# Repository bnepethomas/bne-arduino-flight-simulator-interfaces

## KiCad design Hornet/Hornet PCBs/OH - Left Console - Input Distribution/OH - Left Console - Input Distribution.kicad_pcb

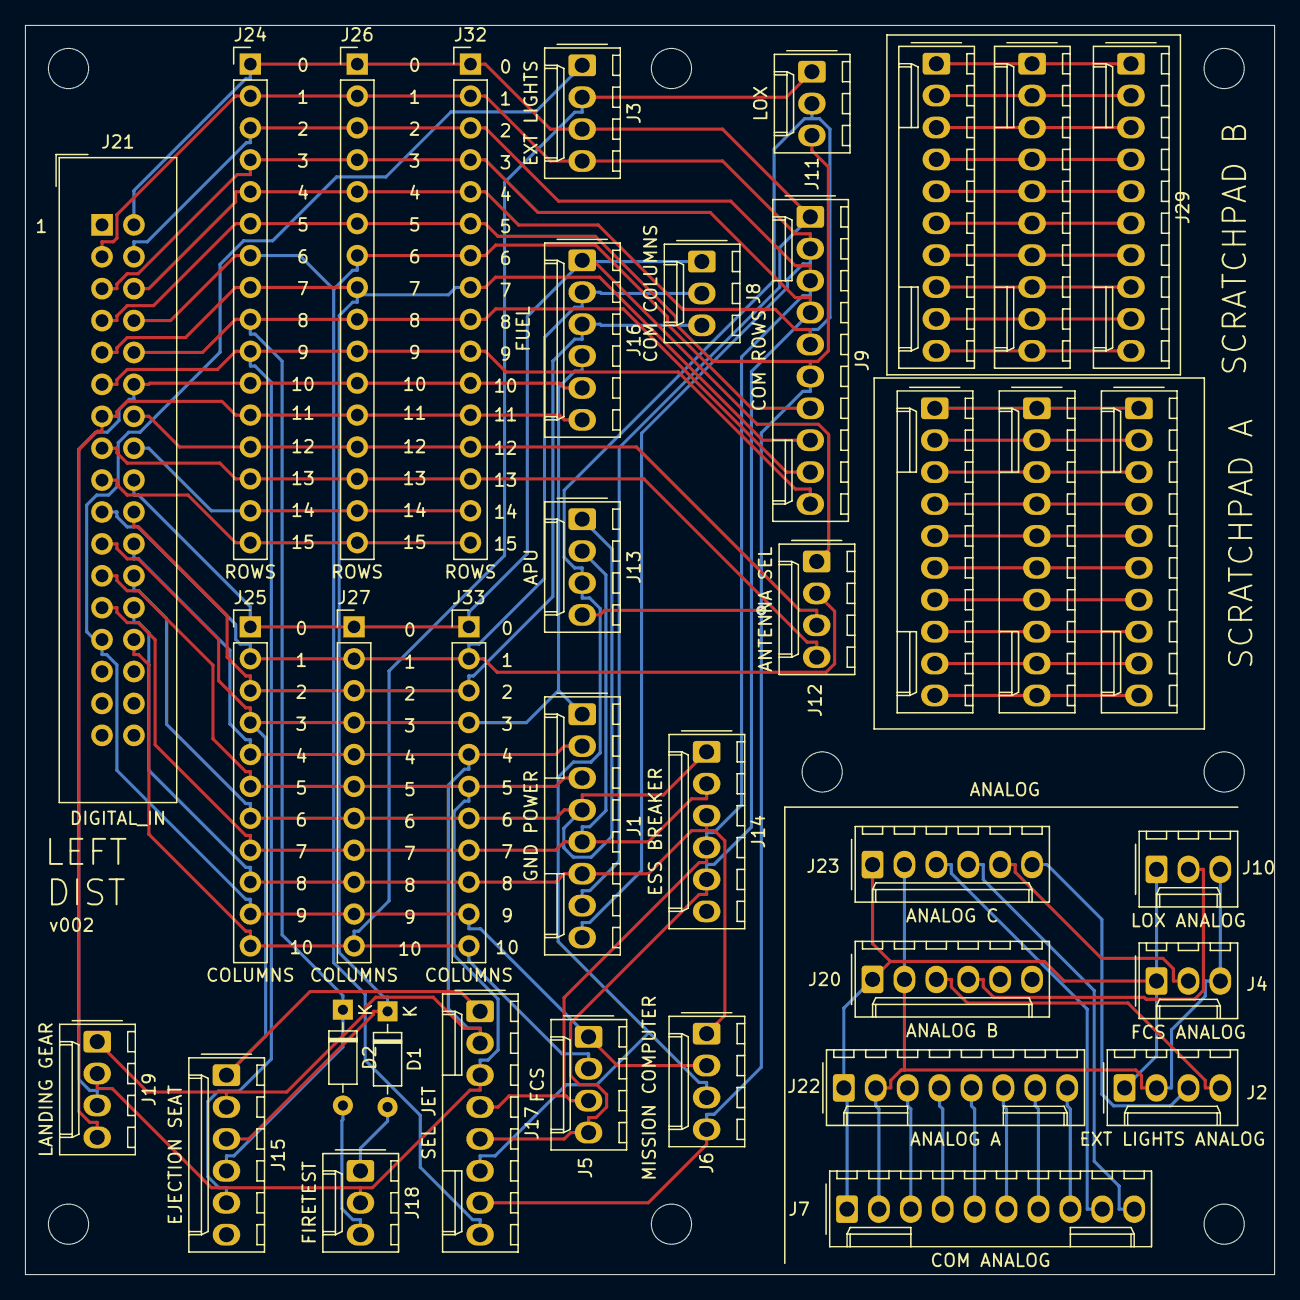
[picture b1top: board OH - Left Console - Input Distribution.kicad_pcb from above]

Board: 2 copper layers, 99.4 x 99.4 mm, 45 parts (0 on the bottom side), 63 nets.

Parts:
D1, D2: D; D_Signal_P7.62mm_Horizontal
H1, H2, H3, H4, H5, H6, H7, H8: MountingHole; MountingHole_3.2mm_M3
J1: GND POWER; Molex_1x08_P2.54mm_Vertical
J2: EXT LIGHTS ANALOG; Molex_1x04_P2.54mm_Vertical
J3: EXT LIGHTS; Molex_1x04_P2.54mm_Vertical
J4: FCS ANALOG; Molex_1x03_P2.54mm_Vertical
J5: FCS; Molex_1x04_P2.54mm_Vertical
J6: MISSION COMPUTER; Molex_1x04_P2.54mm_Vertical
J7: COM ANALOG; Molex_1x10_P2.54mm_Vertical
J8: COM COLUMNS; Molex_1x03_P2.54mm_Vertical
J9: COM ROWS; Molex_1x10_P2.54mm_Vertical
J10: LOX ANALOG; Molex_1x03_P2.54mm_Vertical
J11: LOX; Molex_1x03_P2.54mm_Vertical
J12: ANTENNA SEL; Molex_1x04_P2.54mm_Vertical
J13: APU; Molex_1x04_P2.54mm_Vertical
J14: ESS BREAKER; Molex_1x06_P2.54mm_Vertical
J15: EJECTION SEAT; Molex_1x06_P2.54mm_Vertical
J16: FUEL; Molex_1x06_P2.54mm_Vertical
J17: SEL JET; Molex_1x08_P2.54mm_Vertical
J18: FIRETEST; Molex_1x03_P2.54mm_Vertical
J19: LANDING GEAR; Molex_1x04_P2.54mm_Vertical
J20: ANALOG B; Molex_1x06_P2.54mm_Vertical
J21: DIGITAL_IN; IDC-Header_2x17_P2.54mm_Vertical
J22: ANALOG A; Molex_1x08_P2.54mm_Vertical
J23: ANALOG C; Molex_1x06_P2.54mm_Vertical
J24, J26, J32: ROWS; PinHeader_1x16_P2.54mm_Vertical
J25, J27, J33: COLUMNS; PinHeader_1x11_P2.54mm_Vertical
J28: SpareA1; Molex_1x10_P2.54mm_Vertical
J29: SpareB1; Molex_1x10_P2.54mm_Vertical
J30: SpareA2; Molex_1x10_P2.54mm_Vertical
J31: SpareB2; Molex_1x10_P2.54mm_Vertical
J34: SpareA3; Molex_1x10_P2.54mm_Vertical
J35: SpareB3; Molex_1x10_P2.54mm_Vertical

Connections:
/A1: J28.1, J30.1, J34.1
/A2: J28.2, J30.2, J34.2
/A3: J28.3, J30.3, J34.3
/A4: J28.4, J30.4, J34.4
/A5: J28.5, J30.5, J34.5
/A6: J28.6, J30.6, J34.6
/A7: J28.7, J30.7, J34.7
/A8: J28.8, J30.8, J34.8
/A9: J28.9, J30.9, J34.9
/A10: J28.10, J30.10, J34.10
/ANALOG_5V: J2.1, J4.1, J7.1, J10.1, J20.1, J22.1, J23.1
/ANALOG_GND: J2.2, J4.3, J7.2, J10.3, J20.2, J22.2, J23.2
/B1: J29.1, J31.1, J35.1
/B2: J29.2, J31.2, J35.2
/B3: J29.3, J31.3, J35.3
/B4: J29.4, J31.4, J35.4
/B5: J29.5, J31.5, J35.5
/B6: J29.6, J31.6, J35.6
/B7: J29.7, J31.7, J35.7
/B8: J29.8, J31.8, J35.8
/B9: J29.9, J31.9, J35.9
/B10: J29.10, J31.10, J35.10
/COL0: J8.1, J12.1, J16.1, J21.18, J25.1, J27.1, J33.1
/COL1: J8.2, J12.2, J16.2, J21.19, J25.2, J27.2, J33.2
/COL2: J8.3, J16.3, J21.20, J25.3, J27.3, J33.3
/COL3: J1.1, J15.1, J16.4, J17.1, J21.21, J25.4, J27.4, J33.4
/COL4: J1.2, J15.2, J17.2, J19.1, J21.22, J25.5, J27.5, J33.5
/COL5: J1.3, J17.3, J18.2, J19.2, J21.23, J25.6, J27.6, J33.6
/COL6: J1.4, J13.1, J14.1, J21.24, J25.7, J27.7, J33.7
/COL7: J1.5, J13.2, J14.2, J21.25, J25.8, J27.8, J33.8
/COL8: J1.6, J6.1, J14.3, J21.26, J25.9, J27.9, J33.9
/COL9: J3.1, J5.1, J6.2, J21.27, J25.10, J27.10, J33.10
/COL10: J3.2, J5.2, J11.1, J21.28, J25.11, J27.11, J33.11
/COM_AUX: J7.9, J23.3
/COM_ICS: J7.4, J22.4
/COM_MIDS_A: J7.6, J22.6
/COM_MIDS_B: J7.7, J22.7
/COM_RWR: J7.5, J22.5
/COM_TACAN: J7.8, J22.8
/COM_VOX: J7.3, J22.3
/COM_WPN: J7.10, J23.4
/FORMATION_DIMMER: J2.4, J20.3
/OXY_FLOW: J10.2, J20.4
/POSITION_DIMMER: J2.3, J23.6
/ROW0: J1.7, J3.3, J9.1, J21.2, J24.1, J26.1, J32.1
/ROW1: J1.8, J3.4, J9.2, J21.3, J24.2, J26.2, J32.2
/ROW2: J5.3, J9.3, J14.4, J17.4, J21.4, J24.3, J26.3, J32.3
/ROW3: J5.4, J9.4, J14.5, J17.5, J21.5, J24.4, J26.4, J32.4
/ROW4: J6.3, J9.5, J11.2, J13.3, J17.6, J21.6, J24.5, J26.5, J32.5
/ROW5: J6.4, J9.6, J11.3, J13.4, J17.7, J21.7, J24.6, J26.6, J32.6
/ROW6: J9.7, J17.8, J21.8, J24.7, J26.7, J32.7
/ROW7: D1.1, J9.8, J15.3, J21.9, J24.8, J26.8, J32.8
/ROW8: D2.1, J9.9, J15.4, J21.10, J24.9, J26.9, J32.9
/ROW9: J9.10, J15.5, J21.11, J24.10, J26.10, J32.10
/ROW10: J16.5, J19.3, J21.12, J24.11, J26.11, J32.11
/ROW11: J16.6, J19.4, J21.13, J24.12, J26.12, J32.12
/ROW12: J12.3, J21.14, J24.13, J26.13, J32.13
/ROW13: J12.4, J21.15, J24.14, J26.14, J32.14
/ROW14: J21.16, J24.15, J26.15, J32.15
/ROW15: J21.17, J24.16, J26.16, J32.16
/RUD_TRIM: J4.2, J23.5
unnamed: D1.2, J18.1
unnamed: D2.2, J18.3

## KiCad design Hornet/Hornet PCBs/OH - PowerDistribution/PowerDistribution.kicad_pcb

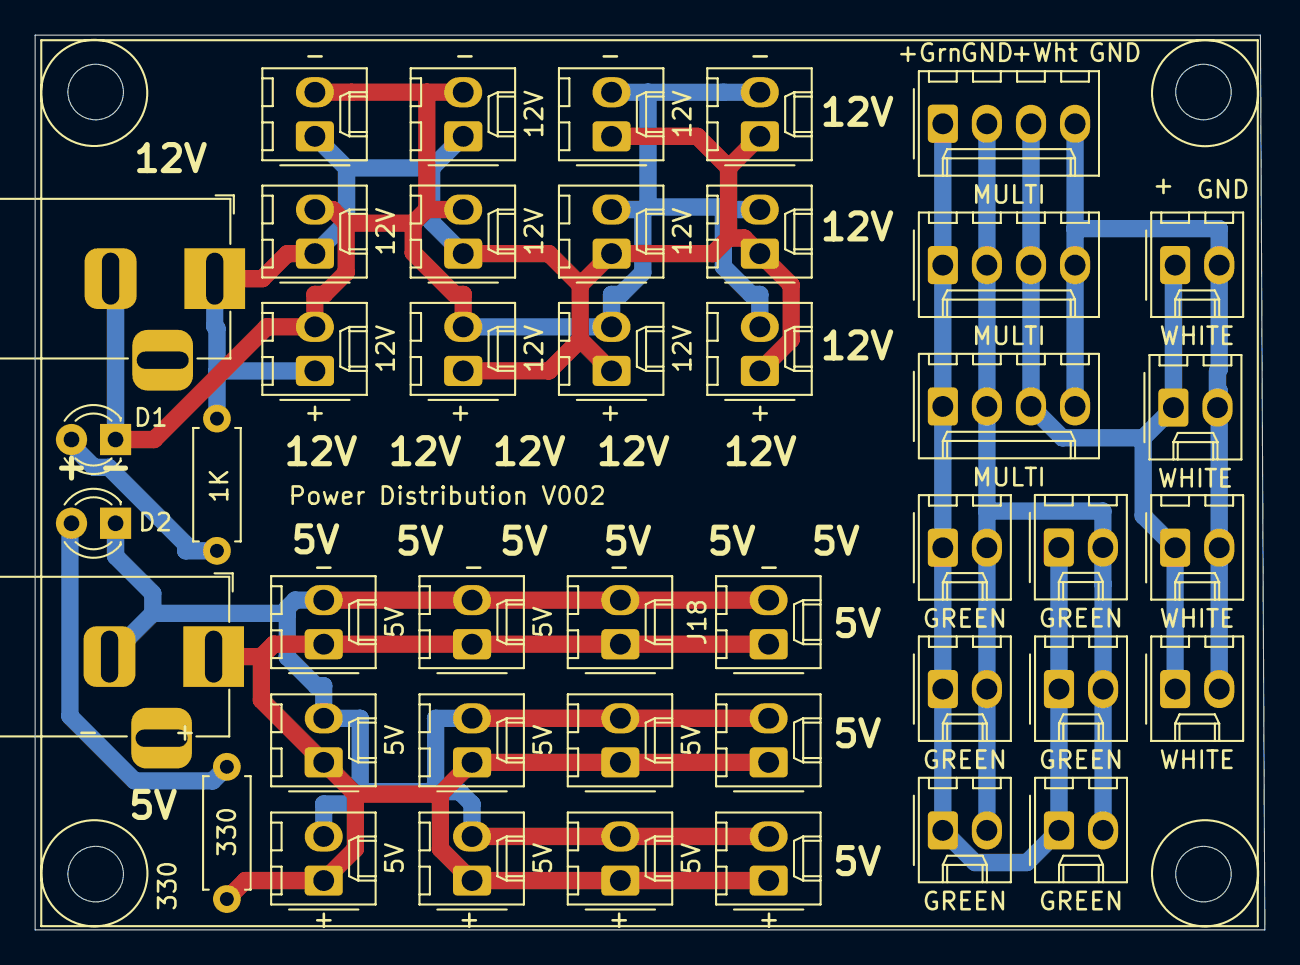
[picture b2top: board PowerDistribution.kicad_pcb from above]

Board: 2 copper layers, 70.9 x 51.6 mm, 48 parts (0 on the bottom side), 10 nets.

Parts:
D1, D2: LED; LED_D3.0mm
H1, H2, H3, H4: MountingHole; MountingHole_3.2mm_M3
J1: 12V; BarrelJack_Horizontal
J2: 5V; BarrelJack_Horizontal
J3, J4, J5: MULTI; Molex_1x04_P2.54mm_Vertical
J6, J7, J11, J12, J16, J17, J23, J24, J28, J29, J34, J35: 12V; Molex_1x02_P2.54mm_Vertical
J8, J9, J14, J15, J21, J22: GREEN; Molex_1x02_P2.54mm_Vertical
J10, J13, J20, J27: WHITE; Molex_1x02_P2.54mm_Vertical
J18, J19, J25, J26, J30, J31, J32, J33, J36, J37, J38, J39: 5V; Molex_1x02_P2.54mm_Vertical
R1: 1K; R_Axial_DIN0207_L6.3mm_D2.5mm_P7.62mm_Horizontal
R2: 330; R_Axial_DIN0207_L6.3mm_D2.5mm_P7.62mm_Horizontal
SPCB1: PT_SmallPCB; PT_General_PCB_Outline

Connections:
/5VGND: D2.1, J2.2, J18.2, J19.2, J25.2, J26.2, J30.2, J31.2, J32.2, J33.2, J36.2, J37.2, J38.2, J39.2
/12VGND: D1.1, J1.2, J6.2, J7.2, J11.2, J12.2, J16.2, J17.2, J23.2, J24.2, J28.2, J29.2, J34.2, J35.2
/+5V: J2.1, J18.1, J19.1, J25.1, J26.1, J30.1, J31.1, J32.1, J33.1, J36.1, J37.1, J38.1, J39.1, R2.1
/+12V: J1.1, J6.1, J7.1, J11.1, J12.1, J16.1, J17.1, J23.1, J24.1, J28.1, J29.1, J34.1, J35.1, R1.1
/Green12V+: J3.1, J4.1, J5.1, J8.1, J9.1, J14.1, J15.1, J21.1, J22.1
/GreenGND: J3.2, J4.2, J5.2, J8.2, J9.2, J14.2, J15.2, J21.2, J22.2
/White+12V: J3.3, J4.3, J5.3, J10.1, J13.1, J20.1, J27.1
/WhiteGND: J3.4, J4.4, J5.4, J10.2, J13.2, J20.2, J27.2
unnamed: D1.2, R1.2
unnamed: D2.2, R2.2

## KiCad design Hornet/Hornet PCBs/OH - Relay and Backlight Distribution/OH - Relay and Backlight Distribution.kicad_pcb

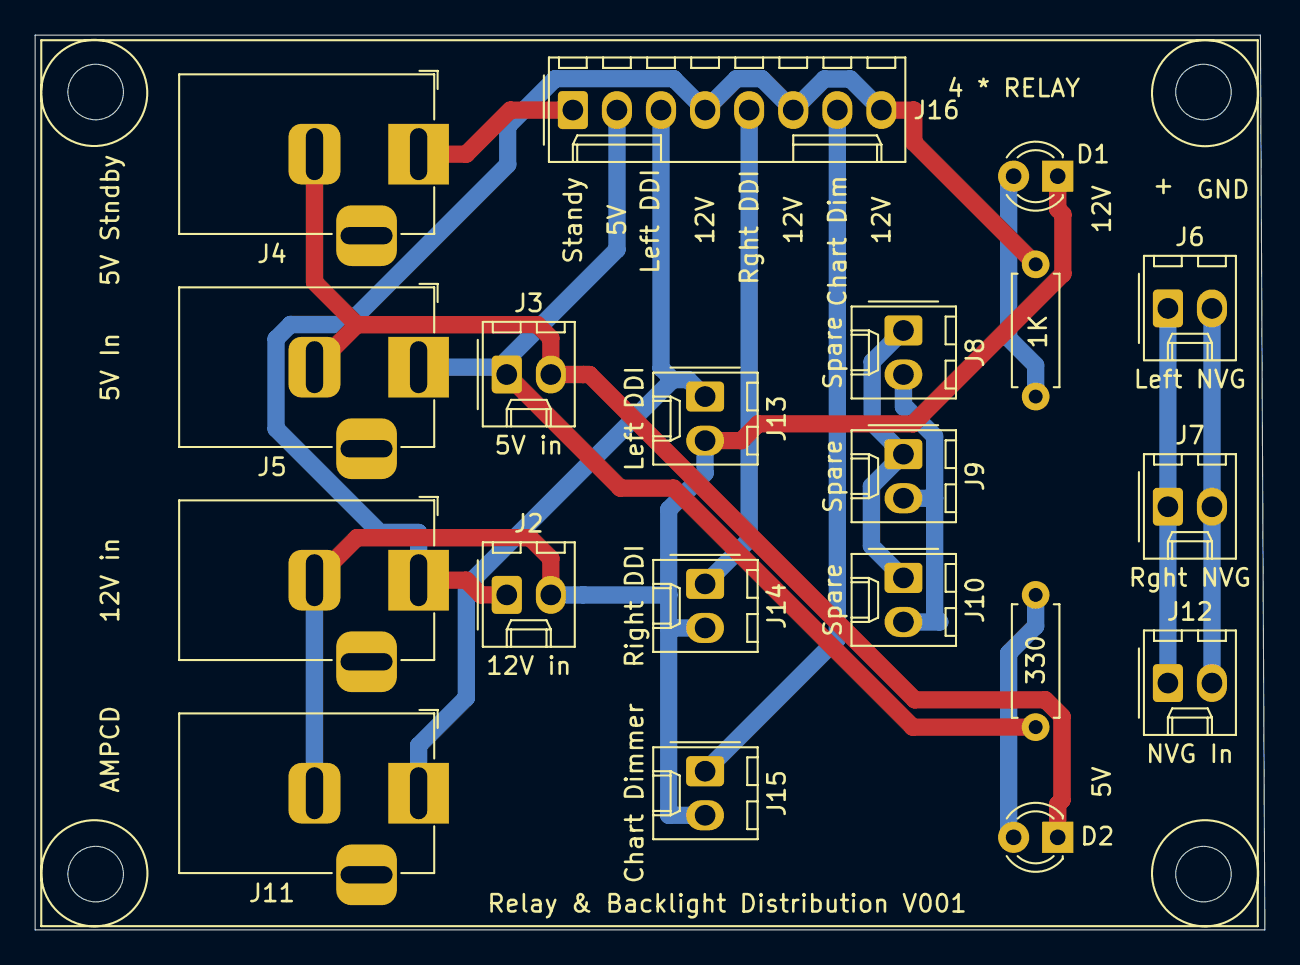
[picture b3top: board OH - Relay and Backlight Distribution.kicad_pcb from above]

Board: 2 copper layers, 70.9 x 51.6 mm, 25 parts (0 on the bottom side), 14 nets.

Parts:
D1, D2: LED; LED_D3.0mm
H1, H2, H3, H4: MountingHole; MountingHole_3.2mm_M3
J1: 12V in; BarrelJack_Horizontal
J2: 12V in; Molex_KK-254_AE-6410-02A_1x02_P2.54mm_Vertical
J3: 5V in; Molex_KK-254_AE-6410-02A_1x02_P2.54mm_Vertical
J4: 5V Stndby; BarrelJack_Horizontal
J5: 5V In; BarrelJack_Horizontal
J6: Left NVG; Molex_KK-254_AE-6410-02A_1x02_P2.54mm_Vertical
J7: Rght NVG; Molex_KK-254_AE-6410-02A_1x02_P2.54mm_Vertical
J8, J9, J10: Spare; Molex_KK-254_AE-6410-02A_1x02_P2.54mm_Vertical
J11: AMPCD; BarrelJack_Horizontal
J12: NVG In; Molex_KK-254_AE-6410-02A_1x02_P2.54mm_Vertical
J13: Left DDI; Molex_KK-254_AE-6410-02A_1x02_P2.54mm_Vertical
J14: Right DDI; Molex_KK-254_AE-6410-02A_1x02_P2.54mm_Vertical
J15: Chart Dimmer; Molex_KK-254_AE-6410-02A_1x02_P2.54mm_Vertical
J16: 4 * RELAY; Molex_KK-254_AE-6410-08A_1x08_P2.54mm_Vertical
R1: 1K; R_Axial_DIN0207_L6.3mm_D2.5mm_P7.62mm_Horizontal
R2: 330; R_Axial_DIN0207_L6.3mm_D2.5mm_P7.62mm_Horizontal
SPCB1: PT_SmallPCB; PT_General_PCB_Outline

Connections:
/5VGND: D2.1, J3.2, J4.2, J5.2
/12VGND: D1.1, J1.2, J2.2, J11.2, J13.2, J14.2, J15.2
/+5VSwitched: J4.1, J16.1
/+5Vin: J3.1, J5.1, J16.2, R2.1
/+12VChartDimmer: J15.1, J16.7
/+12VLeftDDI: J11.1, J13.1, J16.3
/+12VRightDDI: J14.1, J16.5
/+12Vin: J1.1, J2.1, J16.4, J16.6, J16.8, R1.1
/A1: J8.2, J9.2, J10.2
/A2: J8.1, J9.1, J10.1
/NVG+: J6.1, J7.1, J12.1
/NVG-: J6.2, J7.2, J12.2
unnamed: D1.2, R1.2
unnamed: D2.2, R2.2

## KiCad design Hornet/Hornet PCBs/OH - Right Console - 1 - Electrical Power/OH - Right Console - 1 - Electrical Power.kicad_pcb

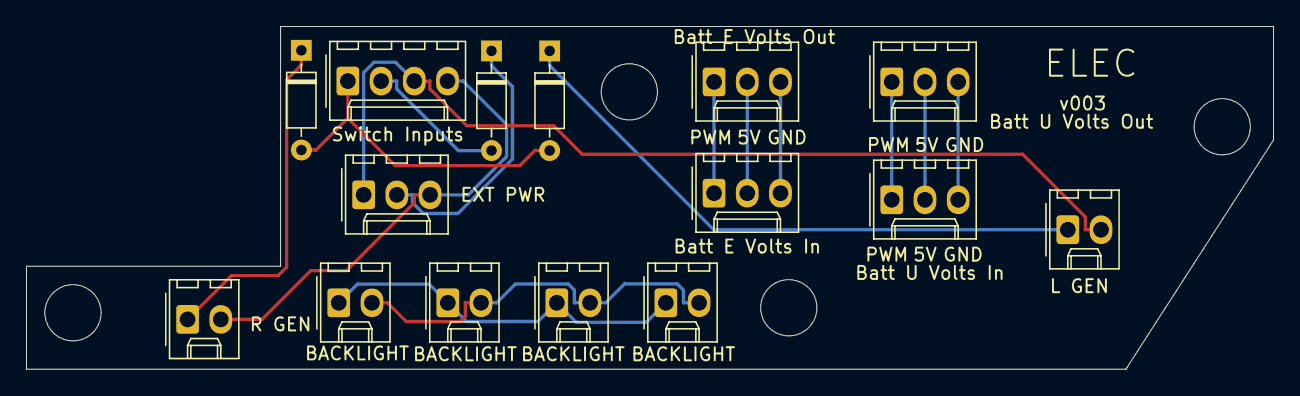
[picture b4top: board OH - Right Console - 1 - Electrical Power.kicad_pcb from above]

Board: 2 copper layers, 95.4 x 26.2 mm, 19 parts (0 on the bottom side), 15 nets.

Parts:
D1, D2, D3: D; D_Signal_P7.62mm_Horizontal
H1, H2, H3, H4: MountingHole; MountingHole_4.3mm_M4
J1: Switch Inputs; Molex_1x04_P2.54mm_Vertical
J2: Batt U Volts In; Molex_1x03_P2.54mm_Vertical
J3: Batt E Volts In; Molex_1x03_P2.54mm_Vertical
J4: Batt U Volts Out; Molex_1x03_P2.54mm_Vertical
J5: Batt E Volts Out; Molex_1x03_P2.54mm_Vertical
J6, J7, J8, J9: BACKLIGHT; Molex_1x02_P2.54mm_Vertical
SW1: EXT PWR; Molex_1x03_P2.54mm_Vertical
SW2: R GEN; Molex_1x02_P2.54mm_Vertical
SW3: L GEN; Molex_1x02_P2.54mm_Vertical

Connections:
/BACKLIGHT+12V: J6.1, J7.1, J8.1, J9.1
/BACKLIGHT-GND: J6.2, J7.2, J8.2, J9.2
/E_5V: J3.2, J5.2
/E_GND: J3.3, J5.3
/E_PWM: J3.1, J5.1
/Row1: J1.3, SW1.1, SW3.2
/Row2: J1.4, SW1.3, SW2.2
/U_5V: J2.2, J4.2
/U_GND: J2.3, J4.3
/U_PWM: J2.1, J4.1
unnamed: D1.1, SW3.1
unnamed: D1.2, D3.2, J1.1
unnamed: D2.1, SW1.2
unnamed: D2.2, J1.2
unnamed: D3.1, SW2.1

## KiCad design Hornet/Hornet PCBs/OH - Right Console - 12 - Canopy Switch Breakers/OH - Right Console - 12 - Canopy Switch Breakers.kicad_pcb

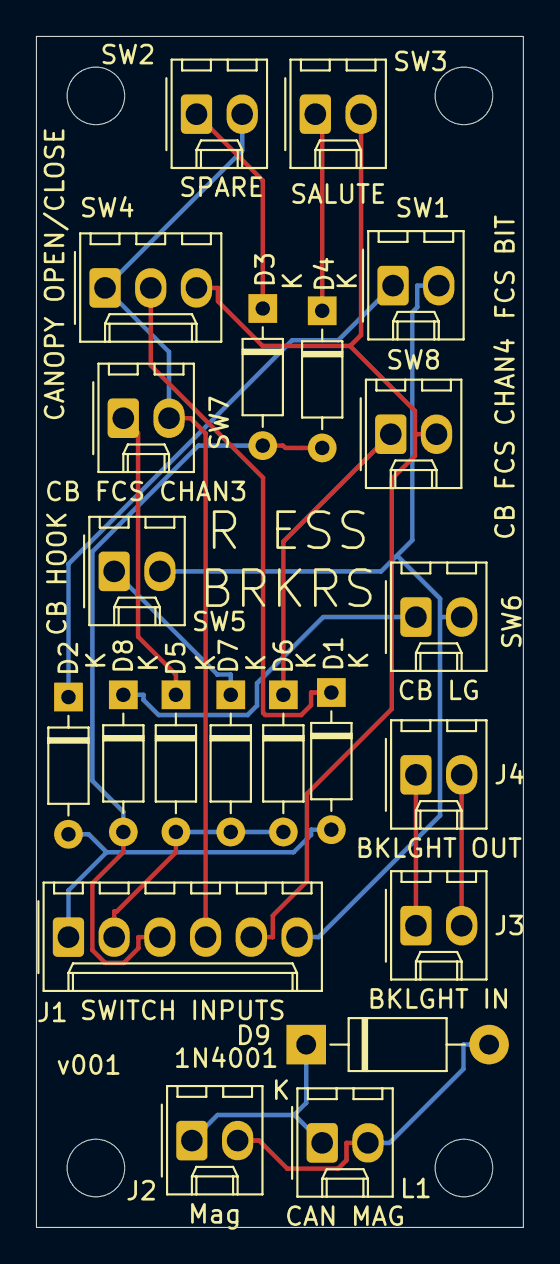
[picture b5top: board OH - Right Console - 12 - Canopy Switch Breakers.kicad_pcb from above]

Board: 2 copper layers, 27.1 x 66.2 mm, 26 parts (0 on the bottom side), 18 nets.

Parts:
D1, D2, D3, D4, D5, D6, D7, D8: D; D_Signal_P7.62mm_Horizontal
D9: 1N4001; D_DO-41_SOD81_P10.16mm_Horizontal
H1, H2, H3, H4: MountingHole; MountingHole_3.2mm_M3
J1: SWITCH INPUTS; Molex_1x06_P2.54mm_Vertical
J2: Mag; Molex_1x02_P2.54mm_Vertical
J3: BKLGHT IN; Molex_1x02_P2.54mm_Vertical
J4: BKLGHT OUT; Molex_1x02_P2.54mm_Vertical
L1: CAN MAG; Molex_1x02_P2.54mm_Vertical
SW1: FCS BIT; Molex_1x02_P2.54mm_Vertical
SW2: SPARE; Molex_1x02_P2.54mm_Vertical
SW3: SALUTE; Molex_1x02_P2.54mm_Vertical
SW4: CANOPY OPEN/CLOSE; Molex_1x03_P2.54mm_Vertical
SW5: CB HOOK; Molex_1x02_P2.54mm_Vertical
SW6: CB LG; Molex_1x02_P2.54mm_Vertical
SW7: CB FCS CHAN3; Molex_1x02_P2.54mm_Vertical
SW8: CB FCS CHAN4; Molex_1x02_P2.54mm_Vertical

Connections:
/Col1: D1.2, D2.2, J1.1
/Col2: D5.2, D6.2, D7.2, J1.2
/Col3: D3.2, D4.2, D8.2, J1.3
/ROW1: J1.4, SW2.2, SW4.1, SW7.2
/ROW2: J1.5, SW3.2, SW4.3, SW8.2
/ROW3: J1.6, SW1.2, SW5.2, SW6.2
unnamed: D1.1, SW4.2
unnamed: D2.1, SW1.1
unnamed: D3.1, SW2.1
unnamed: D4.1, SW3.1
unnamed: D5.1, SW7.1
unnamed: D6.1, SW8.1
unnamed: D7.1, SW5.1
unnamed: D8.1, SW6.1
unnamed: D9.1, J2.1, L1.1
unnamed: D9.2, J2.2, L1.2
unnamed: J3.1, J4.1
unnamed: J3.2, J4.2

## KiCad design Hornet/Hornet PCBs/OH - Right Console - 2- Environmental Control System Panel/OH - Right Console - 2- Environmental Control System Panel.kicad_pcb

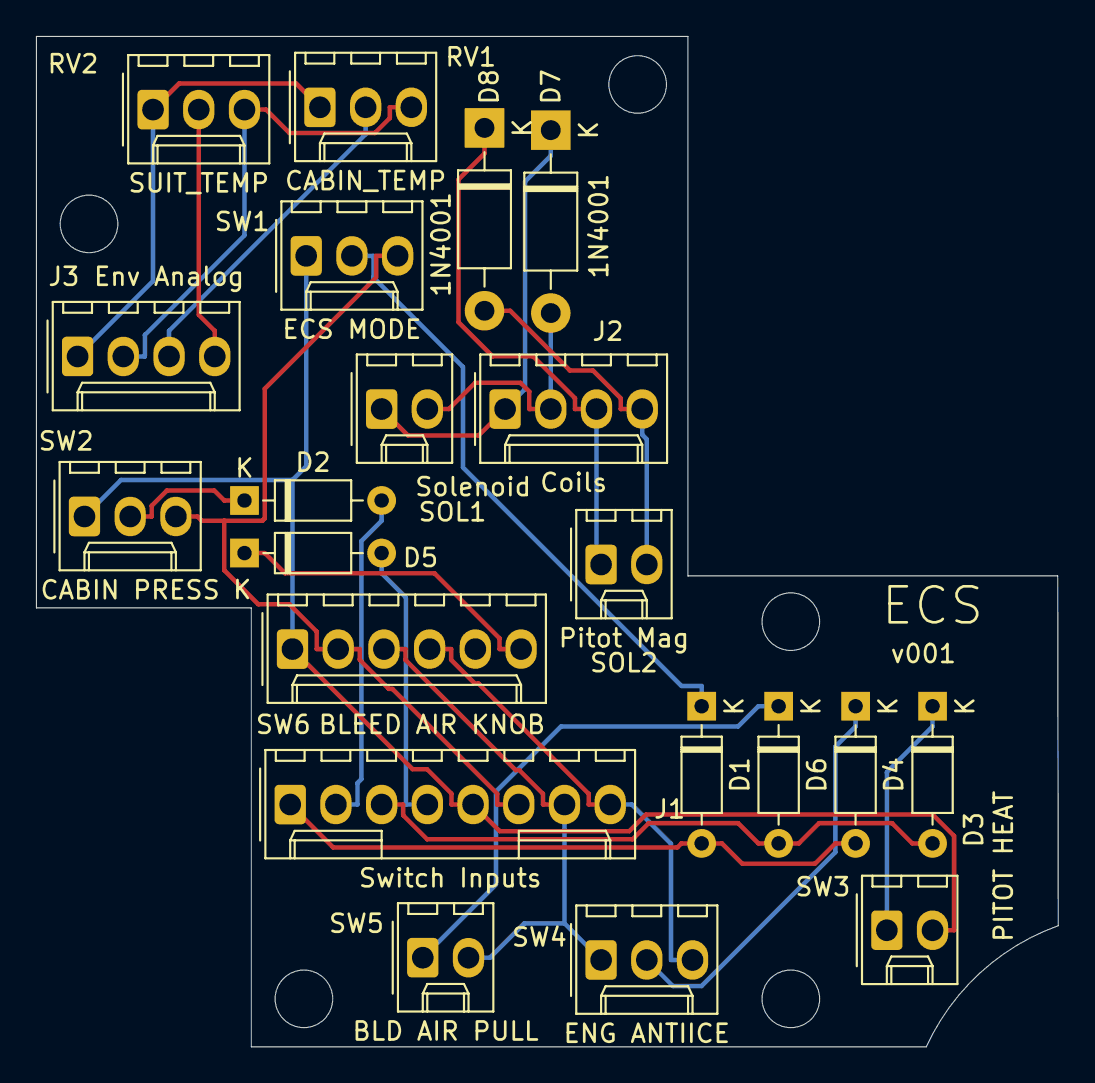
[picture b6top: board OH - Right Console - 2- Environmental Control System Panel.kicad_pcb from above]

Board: 2 copper layers, 56.8 x 56.1 mm, 26 parts (0 on the bottom side), 22 nets.

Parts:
D1, D2, D3, D4, D5, D6: D; D_Signal_P7.62mm_Horizontal
D7, D8: 1N4001; D_DO-41_SOD81_P10.16mm_Horizontal
H1, H2, H3, H4, H5: MountingHole; MountingHole_3.2mm_M3
J1: Switch Inputs; Molex_1x08_P2.54mm_Vertical
J2: Coils; Molex_1x04_P2.54mm_Vertical
J3: Env Analog; Molex_1x04_P2.54mm_Vertical
RV1: CABIN_TEMP; Molex_1x03_P2.54mm_Vertical
RV2: SUIT_TEMP; Molex_1x03_P2.54mm_Vertical
SOL1: Solenoid; Molex_1x02_P2.54mm_Vertical
SOL2: Pitot Mag; Molex_1x02_P2.54mm_Vertical
SW1: ECS MODE; Molex_1x03_P2.54mm_Vertical
SW2: CABIN PRESS; Molex_1x03_P2.54mm_Vertical
SW3: PITOT HEAT; Molex_1x02_P2.54mm_Vertical
SW4: ENG ANTIICE; Molex_1x03_P2.54mm_Vertical
SW5: BLD AIR PULL; Molex_1x02_P2.54mm_Vertical
SW6: BLEED AIR KNOB; Molex_1x06_P2.54mm_Vertical

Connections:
/AnaCabinTemp: J3.3, RV1.2
/AnaSuitTemp: J3.4, RV2.2
/Analog+5V: J3.1, RV1.1, RV2.1
/Analog_Gnd: J3.2, RV1.3, RV2.3
/Bleed_Air_Sol+: D7.1, J2.1, SOL1.1
/Bleed_Air_Sol-: D7.2, J2.2, SOL1.2
/Col1: D1.2, D4.2, J1.1
/Col2: D2.2, J1.2
/Col3: D3.2, D6.2, J1.3
/Col4: D5.2, J1.4
/Pitot_Mag+: D8.1, J2.3, SOL2.1
/Pitot_Mag-: D8.2, J2.4, SOL2.2
/Row1: J1.5, SW1.1, SW2.1, SW3.2, SW6.1
/Row2: J1.6, SW1.3, SW2.3, SW6.2
/Row3: J1.7, SW4.1, SW5.2, SW6.3
/Row4: J1.8, SW4.3, SW6.4
unnamed: D1.1, SW1.2
unnamed: D2.1, SW2.2
unnamed: D3.1, SW3.1
unnamed: D4.1, SW4.2
unnamed: D5.1, SW6.6
unnamed: D6.1, SW5.1

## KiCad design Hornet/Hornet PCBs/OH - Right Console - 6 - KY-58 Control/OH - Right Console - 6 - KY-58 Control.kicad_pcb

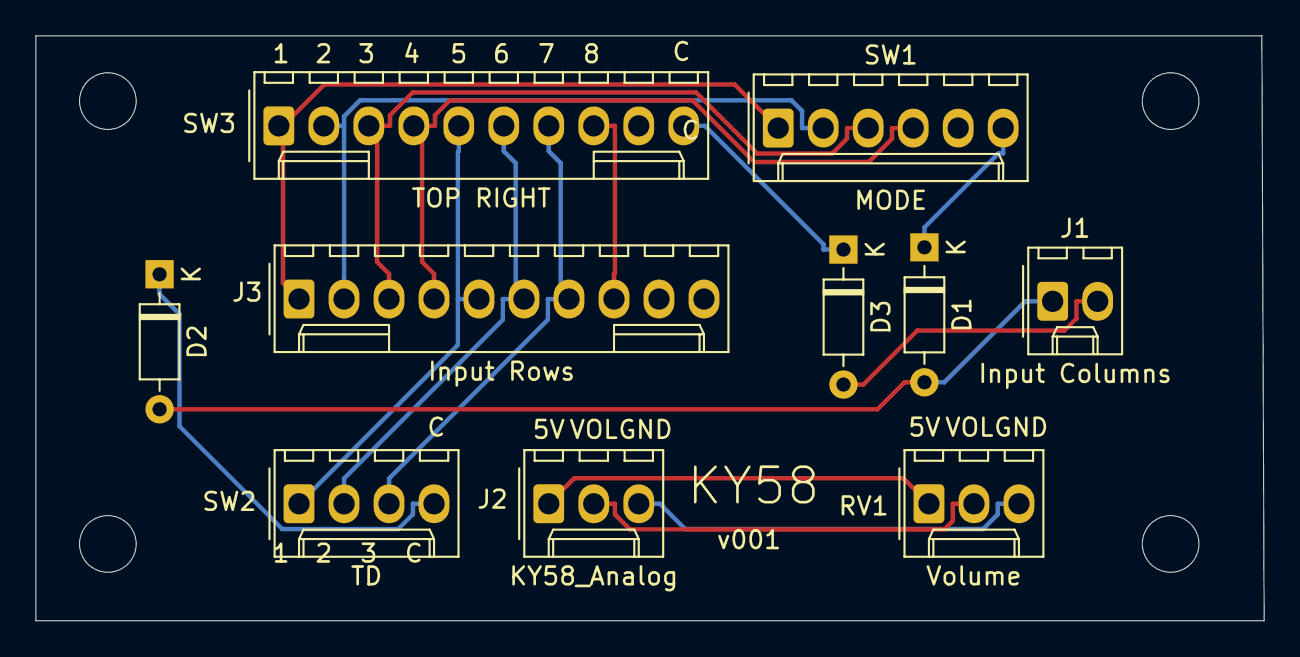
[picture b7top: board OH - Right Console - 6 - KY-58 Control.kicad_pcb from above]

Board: 2 copper layers, 69.3 x 33.0 mm, 14 parts (0 on the bottom side), 16 nets.

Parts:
D1, D2, D3: D; D_Signal_P7.62mm_Horizontal
H1, H2, H3, H4: MountingHole; MountingHole_3.2mm_M3
J1: Input Columns; Molex_1x02_P2.54mm_Vertical
J2: KY58_Analog; Molex_1x03_P2.54mm_Vertical
J3: Input Rows; Molex_1x10_P2.54mm_Vertical
RV1: Volume; Molex_1x03_P2.54mm_Vertical
SW1: MODE; Molex_1x06_P2.54mm_Vertical
SW2: TD; Molex_1x04_P2.54mm_Vertical
SW3: TOP RIGHT; Molex_1x10_P2.54mm_Vertical

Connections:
/Row1: J3.1, SW1.1, SW3.1
/Row2: J3.2, SW1.2, SW3.2
/Row3: J3.3, SW1.3, SW3.3
/Row4: J3.4, SW1.4, SW3.4
/Row5: J3.5, SW2.1, SW3.5
/Row6: J3.6, SW2.2, SW3.6
/Row7: J3.7, SW2.3, SW3.7
/Row8: J3.8, SW3.8
unnamed: D1.1, SW1.6
unnamed: D1.2, D2.2, J1.1
unnamed: D2.1, SW2.4
unnamed: D3.1, SW3.10
unnamed: D3.2, J1.2
unnamed: J2.1, RV1.1
unnamed: J2.2, RV1.2
unnamed: J2.3, RV1.3

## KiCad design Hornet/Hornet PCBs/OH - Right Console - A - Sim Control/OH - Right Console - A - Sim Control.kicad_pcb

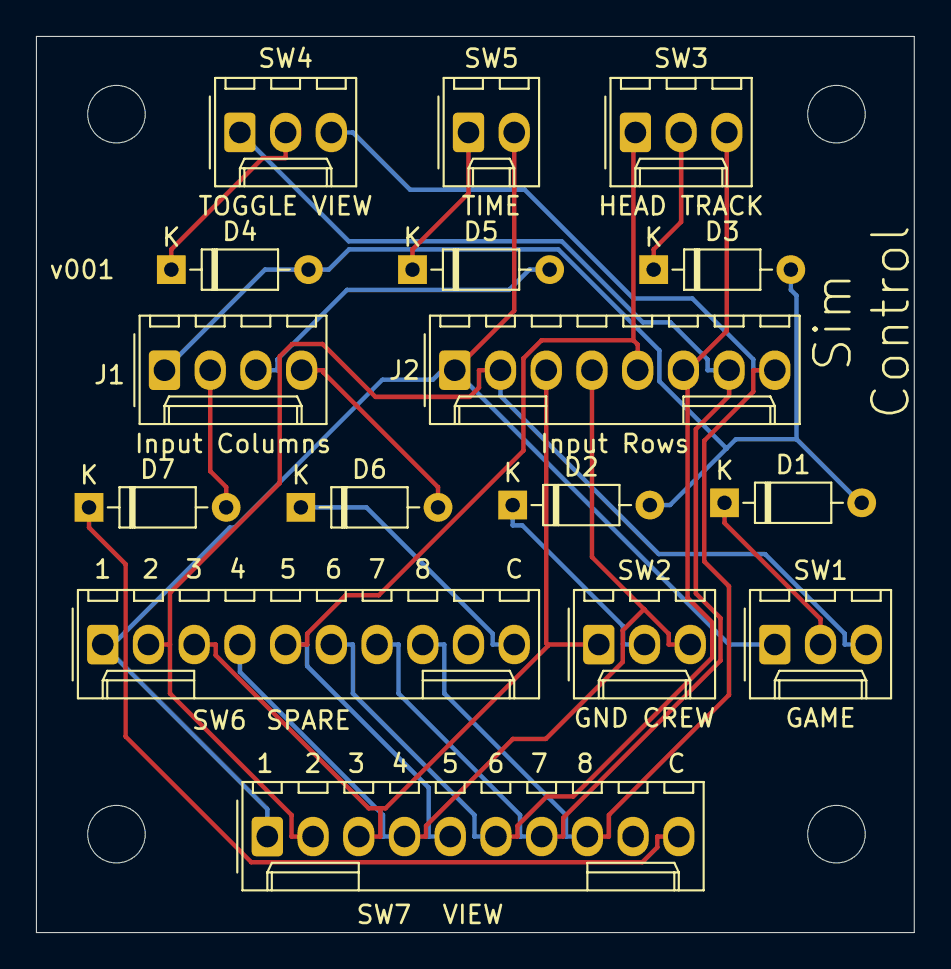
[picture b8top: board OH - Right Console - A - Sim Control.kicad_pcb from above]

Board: 2 copper layers, 48.8 x 49.8 mm, 20 parts (0 on the bottom side), 19 nets.

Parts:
D1, D2, D3, D4, D5, D6, D7: D; D_Signal_P7.62mm_Horizontal
H1, H2, H3, H4: MountingHole; MountingHole_3.2mm_M3
J1: Input Columns; Molex_1x04_P2.54mm_Vertical
J2: Input Rows; Molex_1x08_P2.54mm_Vertical
SW1: GAME; Molex_1x03_P2.54mm_Vertical
SW2: GND CREW; Molex_1x03_P2.54mm_Vertical
SW3: HEAD TRACK; Molex_1x03_P2.54mm_Vertical
SW4: TOGGLE VIEW; Molex_1x03_P2.54mm_Vertical
SW5: TIME; Molex_1x02_P2.54mm_Vertical
SW6: SPARE; Molex_1x10_P2.54mm_Vertical
SW7: VIEW; Molex_1x10_P2.54mm_Vertical

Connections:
/Col1: D1.2, D2.2, D3.2, D4.2, J1.1
/Col2: D7.2, J1.2
/Col3: D5.2, J1.3
/Col4: D6.2, J1.4
/Row1: J2.1, SW1.1, SW5.2, SW6.1, SW7.1
/Row2: J2.2, SW1.3, SW6.2, SW7.2
/Row3: J2.3, SW2.1, SW6.3, SW7.3
/Row4: J2.4, SW2.3, SW6.4, SW7.4
/Row5: J2.5, SW3.1, SW6.5, SW7.5
/Row6: J2.6, SW3.3, SW6.6, SW7.6
/Row7: J2.7, SW4.1, SW6.7, SW7.7
/Row8: J2.8, SW4.3, SW6.8, SW7.8
unnamed: D1.1, SW1.2
unnamed: D2.1, SW2.2
unnamed: D3.1, SW3.2
unnamed: D4.1, SW4.2
unnamed: D5.1, SW5.1
unnamed: D6.1, SW6.10
unnamed: D7.1, SW7.10
